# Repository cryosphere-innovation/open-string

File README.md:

# OpenString

<!-- SPDX-License-Identifier: CC-BY-SA-4.0 -->
<!-- Copyright (c) 2026 Cryosphere Innovation (a wholly owned subsidiary of JASCO Applied Sciences). -->
<!-- Contact: Dr. Cameron Planck <cjp@cryosphereinnovation.com> -->

OpenString is the world's first open-source temperature string for environmental monitoring. It consists of a PCB design, firmware package, and assembly guide to help you bring temperature profile monitoring into any project.

Based on the production temperature string used by [SIMB3](https://cryosphereinnovation.com/simb3), OpenString is an extensible, arctic-hardened design that can be used as-is or tailored to your specific application. Everything you need to build, flash, and deploy one is in this repo.

> **Don't want to build your own?** Cryosphere Innovation can supply ready-to-use, assembled OpenString boards. Email [cjp@cryosphereinnovation.com](mailto:cjp@cryosphereinnovation.com) for pricing and lead time.

## Repository layout

| Path        | Contents                                                     |
| ----------- | ------------------------------------------------------------ |
| `hardware/` | KiCad project, schematic, PCB, Gerbers, BOM, fab-house notes |
| `firmware/` | Arduino sketch for the microcontroller (single `.ino` file)  |
| `docs/`     | Markdown (MDX) source rendered on the Cryosphere docs site   |
| `LICENSES/` | Full text of each license used in the project                |
| `LICENSE`   | Top-level license map                                        |

## Build your own

1. Read [`docs/ordering.mdx`](./docs/ordering.mdx) to order the PCB and parts.
2. Follow [`docs/open-string-assembly.mdx`](./docs/open-string-assembly.mdx) for the multi-step assembly walkthrough (soldering, housing, potting, testing).
3. Flash the firmware (see below, or [`docs/firmware.mdx`](./docs/firmware.mdx)).
4. Deploy.

## Hardware

The KiCad project and fabrication outputs live in `hardware/`:

- `hardware/board-files/` — KiCad project (schematic, PCB layout, project settings)
- `hardware/fabrication/gerbers/` — Gerbers and drill files ready to upload to a PCB house

See [`docs/ordering.mdx`](./docs/ordering.mdx) for the current ordering guide
(fab house settings, stencil, assembly options, expected cost).

Hardware design files are released under **CERN-OHL-S 2.0**
([`LICENSES/CERN-OHL-S-2.0.txt`](./LICENSES/CERN-OHL-S-2.0.txt)).

## Firmware

Single-file Arduino sketch at
[`firmware/src/open_string.ino`](./firmware/src/open_string.ino). PlatformIO
project config at [`platformio.ini`](./platformio.ini). Target board:
**Adafruit Feather M0** (SAMD21).

### Building with PlatformIO (recommended)

1. Install [PlatformIO Core](https://docs.platformio.org/page/core/installation.html)
   (or the PlatformIO IDE extension for VS Code).
2. From the repo root (the folder containing `platformio.ini`):
   ```sh
   pio run                  # compile
   pio run --target upload  # flash over USB
   pio device monitor       # open serial console at 115200 baud
   ```
   PlatformIO installs the SAMD board support and the OneWire library
   automatically based on `platformio.ini`.

   In VS Code, open the repo root as the workspace folder so the
   PlatformIO extension can find `platformio.ini`.

### Building with the Arduino IDE

1. Install the [Arduino IDE](https://www.arduino.cc/en/software) (or
   `arduino-cli`) and the SAMD board support package.
2. The Arduino IDE expects the sketch folder name to match the `.ino`
   filename — rename `firmware/src/` to `firmware/open_string/` (or
   symlink it) and open `open_string.ino` from there.
3. Select **Adafruit Feather M0** as the board, pick the right port,
   and click **Upload**.

See [`docs/firmware.mdx`](./docs/firmware.mdx) for the full flashing
guide, including fuse settings and troubleshooting.

Firmware source is released under **GPL-3.0**
([`LICENSES/GPL-3.0.txt`](./LICENSES/GPL-3.0.txt)).

## License

OpenString is multi-licensed. See [`LICENSE`](./LICENSE) for the full map.
Summary:

- **Hardware** — CERN-OHL-S 2.0
- **Firmware** — GPL-3.0
- **Documentation** — CC-BY-SA-4.0

All three allow commercial use and require attribution. Derivative works
must remain open under the same license.

## How the docs are published

The OpenString documentation lives at
[cryosphereinnovation.com/docs](https://cryosphereinnovation.com/docs).
The live site bakes the MDX files in `docs/` into its build output
when it deploys, so changes here go live the next time the docs site
rebuilds.

`docs/manifest.json` is generated automatically by a GitHub Action
(`.github/workflows/manifest.yml`) on every push that touches an MDX
file. You don't need to edit it by hand — just add/edit `.mdx` files
and push.

## Contributing

Issues and pull requests welcome. By contributing, you agree to license
your contribution under the license that applies to the directory you
are contributing to (see [`LICENSE`](./LICENSE)).

## Maintainer and contact

OpenString is maintained by **Cryosphere Innovation** (a wholly owned
subsidiary of JASCO Applied Sciences). Primary contact:
**Dr. Cameron Planck** — <cjp@cryosphereinnovation.com>.

Contributors are listed in [`AUTHORS.md`](./AUTHORS.md).

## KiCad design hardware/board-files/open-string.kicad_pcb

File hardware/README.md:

# Hardware

<!-- SPDX-License-Identifier: CC-BY-SA-4.0 -->

KiCad project and fabrication outputs for the OpenString PCB and cable
assembly.

## Contents

- `board-files/` — KiCad project (schematic, PCB layout, project settings)
- `fabrication/gerbers/` — Gerbers and drill files ready to upload to a PCB house

## Ordering

See [`docs/ordering.mdx`](../docs/ordering.mdx) for the current ordering
guide (fab house settings, stencil, assembly options, expected cost).

## License

Hardware design files in this directory are released under
**CERN-OHL-S 2.0**. See [`../LICENSE`](../LICENSE) and
[`../LICENSES/CERN-OHL-S-2.0.txt`](../LICENSES/CERN-OHL-S-2.0.txt).

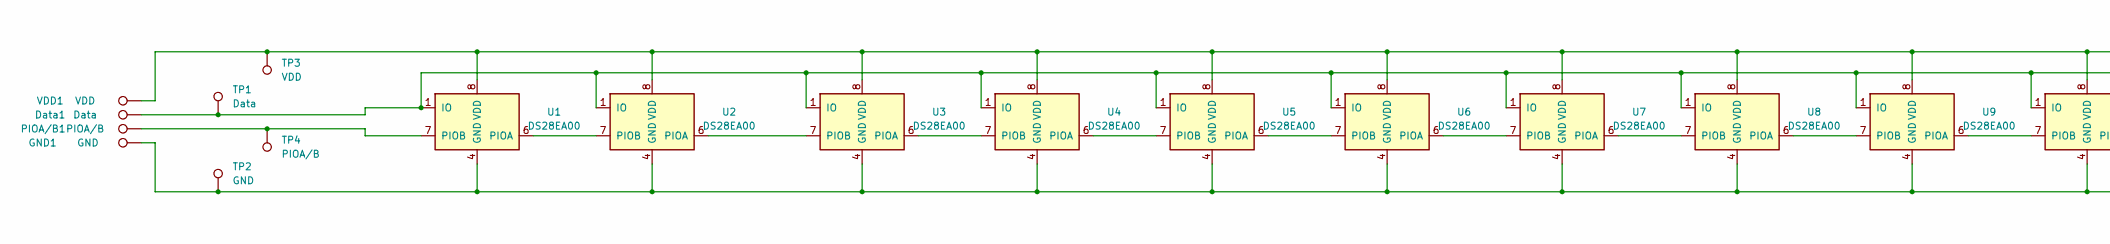
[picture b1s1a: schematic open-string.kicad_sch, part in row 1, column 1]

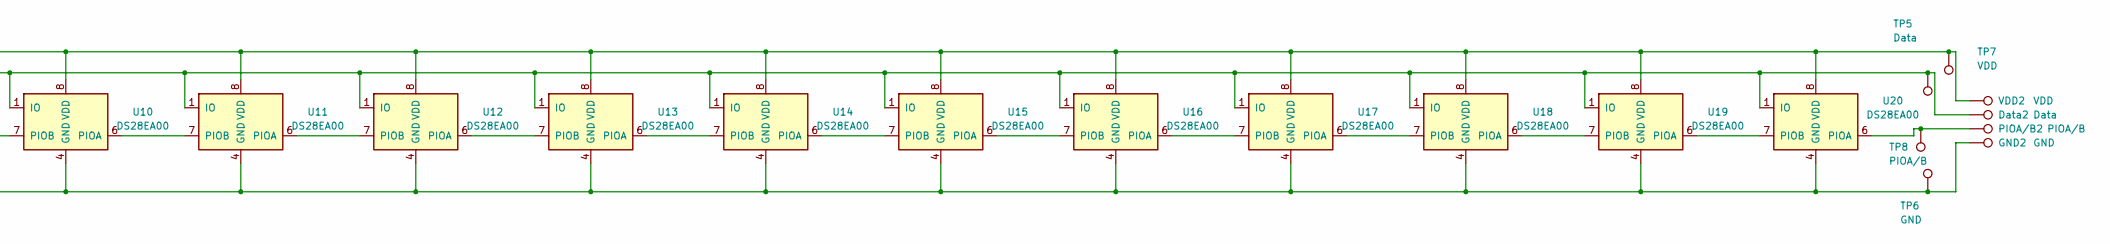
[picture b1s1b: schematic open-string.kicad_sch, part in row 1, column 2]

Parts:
Data1, Data2: Data; TestPoint_THTPad_2.0x2.0mm_Drill1.0mm
GND1, GND2: GND; TestPoint_THTPad_2.0x2.0mm_Drill1.0mm
PIOA/B1, PIOA/B2: PIOA/B; TestPoint_THTPad_2.0x2.0mm_Drill1.0mm
TP1, TP5: Data; TestPoint_Pad_D1.5mm
TP2, TP6: GND; TestPoint_Pad_D1.5mm
TP3, TP7: VDD; TestPoint_Pad_D1.5mm
TP4, TP8: PIOA/B; TestPoint_Pad_D1.5mm
U1, U2, U3, U4, U5, U6, U7, U8, U9, U10, U11, U12, U13, U14, U15, U16, U17, U18, U19, U20: DS28EA00; MSOP-8_3x3mm_P0.65mm
VDD1, VDD2: VDD; TestPoint_THTPad_2.0x2.0mm_Drill1.0mm

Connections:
unnamed: GND1.1, GND2.1, TP2.1, TP6.1, U1.4 (GND), U2.4 (GND), U3.4 (GND), U4.4 (GND), U5.4 (GND), U6.4 (GND), U7.4 (GND), U8.4 (GND), U9.4 (GND), U10.4 (GND), U11.4 (GND), U12.4 (GND), U13.4 (GND), U14.4 (GND), U15.4 (GND), U16.4 (GND), U17.4 (GND), U18.4 (GND), U19.4 (GND), U20.4 (GND)
unnamed: Data1.1, Data2.1, TP1.1, TP5.1, U1.1 (IO), U2.1 (IO), U3.1 (IO), U4.1 (IO), U5.1 (IO), U6.1 (IO), U7.1 (IO), U8.1 (IO), U9.1 (IO), U10.1 (IO), U11.1 (IO), U12.1 (IO), U13.1 (IO), U14.1 (IO), U15.1 (IO), U16.1 (IO), U17.1 (IO), U18.1 (IO), U19.1 (IO), U20.1 (IO)
unnamed: U1.6 (PIOA), U2.7 (PIOB)
unnamed: PIOA/B1.1, TP4.1, U1.7 (PIOB)
unnamed: TP3.1, TP7.1, U1.8 (VDD), U2.8 (VDD), U3.8 (VDD), U4.8 (VDD), U5.8 (VDD), U6.8 (VDD), U7.8 (VDD), U8.8 (VDD), U9.8 (VDD), U10.8 (VDD), U11.8 (VDD), U12.8 (VDD), U13.8 (VDD), U14.8 (VDD), U15.8 (VDD), U16.8 (VDD), U17.8 (VDD), U18.8 (VDD), U19.8 (VDD), U20.8 (VDD), VDD1.1, VDD2.1
unnamed: U2.6 (PIOA), U3.7 (PIOB)
unnamed: U3.6 (PIOA), U4.7 (PIOB)
unnamed: U4.6 (PIOA), U5.7 (PIOB)
unnamed: U5.6 (PIOA), U6.7 (PIOB)
unnamed: U6.6 (PIOA), U7.7 (PIOB)
unnamed: U7.6 (PIOA), U8.7 (PIOB)
unnamed: U8.6 (PIOA), U9.7 (PIOB)
unnamed: U10.6 (PIOA), U11.7 (PIOB)
unnamed: U9.6 (PIOA), U10.7 (PIOB)
unnamed: U11.6 (PIOA), U12.7 (PIOB)
unnamed: U12.6 (PIOA), U13.7 (PIOB)
unnamed: U13.6 (PIOA), U14.7 (PIOB)
unnamed: U14.6 (PIOA), U15.7 (PIOB)
unnamed: U15.6 (PIOA), U16.7 (PIOB)
unnamed: U16.6 (PIOA), U17.7 (PIOB)
unnamed: U17.6 (PIOA), U18.7 (PIOB)
unnamed: U18.6 (PIOA), U19.7 (PIOB)
unnamed: U19.6 (PIOA), U20.7 (PIOB)
unnamed: PIOA/B2.1, TP8.1, U20.6 (PIOA)

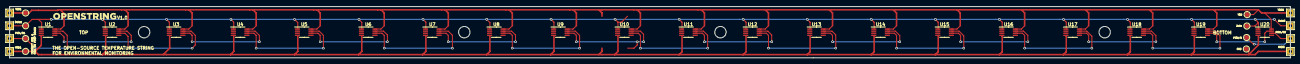
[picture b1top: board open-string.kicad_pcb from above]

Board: 2 copper layers, 400.0 x 16.0 mm, 36 parts (0 on the bottom side), 24 nets.

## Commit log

2026-04-24 Initial commit: open-string hardware, firmware, and docs
2026-04-24 Add docs frontmatter for cryosphere docs site integration
    Populate title, slug, status, category, heading, and date fields on each
    doc so the cryosphere build pipeline can index and publish these pages.
    Also fix three stale GitHub URLs that pointed at cameronplanck/open-string
    instead of cryosphere-innovation/open-string.
2026-04-24 Add docs manifest generator and GitHub Action
    The cryosphere docs site fetches this manifest at build/revalidate time
    to list available docs without hitting the GitHub API for a directory
    listing (no rate limits, one request instead of N).
    The workflow regenerates manifest.json on every push that touches an
    MDX file and auto-commits the result back to main. Path filter excludes
    manifest.json so the auto-commit doesn't re-trigger the workflow.
2026-04-24 Document how docs are published to the cryosphere site
    Clarify in the README that docs/ feeds the live cryosphere docs site via
    runtime fetch, and that manifest.json is auto-generated — contributors
    only need to edit .mdx files.
2026-04-24 Rewrite intro page with Arctic-proven track record and template framing
    Lead with the production context (three years inside SIMB3 across ~40
    Arctic/Antarctic deployments) to establish credibility, then describe
    the PCB form factor and the "template you can build on" framing before
    the license / start-here sections.
2026-04-24 Refine intro: tighten opening summary, link SIMB3 and limits page
    Restructure the lead paragraph to describe OpenString as a PCB (not a
    cable), and link the 'continuous span of any length' claim to the
    hardware reference where practical limits belong. Also link the first
    mention of SIMB3.
2026-04-24 Add arctic-hardened / SIMB3-since-2023 positioning to intro
    Lead with the 'hardened, extensible platform' framing right after the
    first sentence, and compress the later SIMB3 reference into a single
    production-track-record line to avoid repeating the same facts twice.
2026-04-24 Tighten lead paragraph, drop 'extensible platform'
    Strong first sentence (open-source, arctic-hardened, for environmental
    monitoring), then a second sentence that makes the reuse point (fork
    the whole design or take just the PCB/firmware) and closes with SIMB3
    as the proof point.
2026-04-29 Consolidate firmware into a single sketch and merge project READMEs
2026-05-04 Restructure docs and add SIMB3 assembly content
    Reorganize the documentation set around a multi-page assembly section
    mirroring the SIMB3 production workflow:
    - Replace the single-file assembly.mdx with five new pages: an overview
    plus Prepare Housing, Assemble Boards, Potting, and Mount & Validate.
    - Add temperature-string assembly imagery (19 photos) and Mux video IDs
    for the soldering, housing, potting, and validation walkthroughs.
2026-05-04 Auto-regenerate docs/manifest.json
2026-05-05 Rename Mount & Validate → Testing & Mount
    Display name change in the page title, manifest, and the assembly
    overview's step list. Slug stays open-string-mount-validate so URLs
    don't break.
    The order matches the page body: electrical test first, then bond to
    the mounting surface (VHB tape).
2026-05-05 Rename mount-validate → testing slug; refresh README
    - File rename: docs/open-string-mount-validate.mdx → docs/open-string-testing.mdx
    - Frontmatter slug, manifest entry, and cross-references in
    open-string-assembly.mdx, open-string-assembly-solder.mdx, and
    open-string-potting.mdx all updated.
    README.md:
    - Lead rewritten to match the docs intro: "the world's first
2026-05-05 Add pull-up resistor callout in testing doc; assembly intro tweaks
    testing.mdx:
    - Add a "Pull-up resistor required" warning callout right after the
    wiring steps. Explains the 4.7 kΩ between data and 3.3 V supply,
    with a note that long cable runs may need a stronger pull-up
    (e.g. 2.2 kΩ).
    - Add the resistor to the parts list.
